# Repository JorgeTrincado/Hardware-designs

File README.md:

# Hardware-designs

This work is licensed under a Creative Commons Attribution-ShareAlike 4.0 International License.

This means you are free to use this design in any way you like (this includes commercial use) as long as you credit me. If you choose to modify the design files, you should share the modified design files under the same license.

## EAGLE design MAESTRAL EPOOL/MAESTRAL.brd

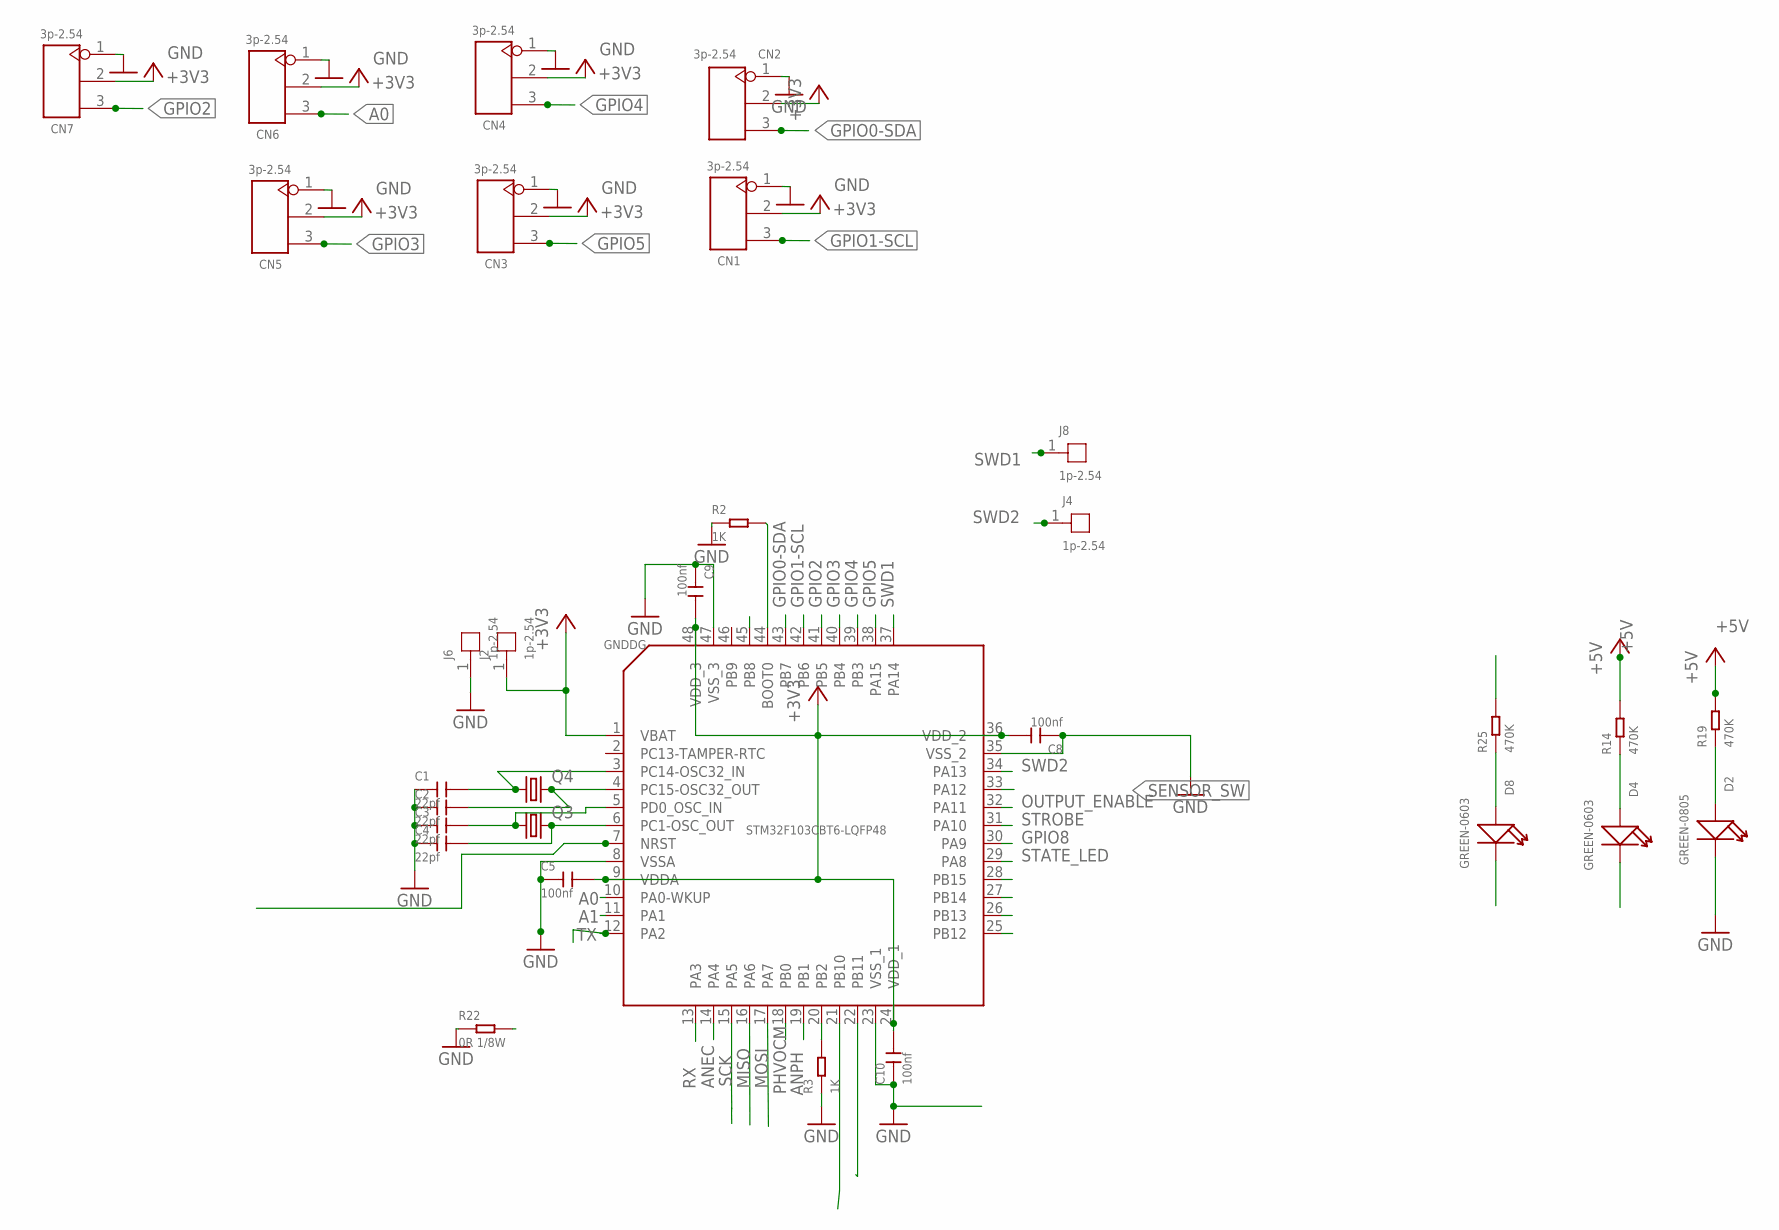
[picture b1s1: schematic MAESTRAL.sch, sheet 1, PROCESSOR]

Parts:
C1, C2, C3, C4: 22pf; C0603
C5, C8, C9, C10: 100nf; C0603
CN1, CN2, CN3, CN4, CN5, CN6, CN7: 3p-2.54; H3-2.54
D2: GREEN-0805; LED-0805
D4, D8: GREEN-0603; LED-0603
GNDDG: STM32F103CBT6-LQFP48; LQFP48-0.5-7X7MM
J2, J4, J6, J8: 1p-2.54; 1P-65/35MIL
Q3: CRYSTALSM49; SM49
Q4: CRYSTALMM20SS; MM20SS
R2, R3: 1K; R0603
R14, R19, R25: 470K; R0603
R22: 0R 1/8W; R0805

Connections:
+3V3: C5.2, C8.2, C9.2, C10.2, CN1.2, CN2.2, CN3.2, CN4.2, CN5.2, CN6.2, CN7.2, GNDDG.1 (VBAT), GNDDG.9 (VDDA), GNDDG.24 (VDD_1), GNDDG.36 (VDD_2), GNDDG.48 (VDD_3), J2.1; also elsewhere on the board
+5V: R14.2, R19.2; also elsewhere on the board
A0: CN6.3, GNDDG.10 (PA0-WKUP)
A1: GNDDG.11 (PA1); also elsewhere on the board
ANEC: GNDDG.14 (PA4); also elsewhere on the board
ANPH: GNDDG.19 (PB1); also elsewhere on the board
ECGND: D4.-; also elsewhere on the board
GND: CN1.1, CN2.1, CN3.1, CN4.1, CN5.1, CN6.1, CN7.1, D2.-, R22.1; also elsewhere on the board
GNDDG: C1.1, C2.1, C3.1, C4.1, C5.1, C8.1, C9.1, C10.1, D8.-, GNDDG.8 (VSSA), GNDDG.23 (VSS_1), GNDDG.35 (VSS_2), GNDDG.47 (VSS_3), J6.1, R2.1, R3.1, R22.2; also elsewhere on the board
GPIO0-SDA: CN2.3, GNDDG.43 (PB7)
GPIO1-SCL: CN1.3, GNDDG.42 (PB6)
GPIO2: CN7.3, GNDDG.41 (PB5)
GPIO3: CN5.3, GNDDG.40 (PB4)
GPIO4: CN4.3, GNDDG.39 (PB3)
GPIO5: CN3.3, GNDDG.38 (PA15)
GPIO8: GNDDG.30 (PA9)
MISO: GNDDG.16 (PA6); also elsewhere on the board
MISO-SDO: GNDDG.27 (PB14); also elsewhere on the board
MOSI: GNDDG.17 (PA7); also elsewhere on the board
MOSI-SDI: GNDDG.28 (PB15); also elsewhere on the board
unnamed: C2.2, GNDDG.4 (PC15-OSC32_OUT), Q4.4 (2)
unnamed: C1.2, GNDDG.3 (PC14-OSC32_IN), Q4.1
unnamed: C4.2, GNDDG.6 (PC1-OSC_OUT), Q3.2
unnamed: C3.2, GNDDG.5 (PD0_OSC_IN), Q3.1
unnamed 35: GNDDG.7 (NRST); also elsewhere on the board
unnamed: GNDDG.20 (PB2), R3.2
unnamed: GNDDG.44 (BOOT0), R2.2
unnamed: D8.+, R25.1
unnamed: GNDDG.45 (PB8), R25.2
unnamed: D4.+, R14.1
unnamed: D2.+, R19.1
OUTPUT_ENABLE: GNDDG.32 (PA11); also elsewhere on the board
PHCS: GNDDG.25 (PB12); also elsewhere on the board
PHVOCM: GNDDG.18 (PB0); also elsewhere on the board
RX: GNDDG.13 (PA3); also elsewhere on the board
SCK: GNDDG.15 (PA5); also elsewhere on the board
SCL2: GNDDG.21 (PB10); also elsewhere on the board
SCLK: GNDDG.26 (PB13); also elsewhere on the board
SDA2: GNDDG.22 (PB11); also elsewhere on the board
SENSOR_SW: GNDDG.33 (PA12); also elsewhere on the board
STATE_LED: GNDDG.29 (PA8)
STROBE: GNDDG.31 (PA10); also elsewhere on the board
SWD1: GNDDG.37 (PA14), J8.1
SWD2: GNDDG.34 (PA13), J4.1
TX: GNDDG.12 (PA2); also elsewhere on the board

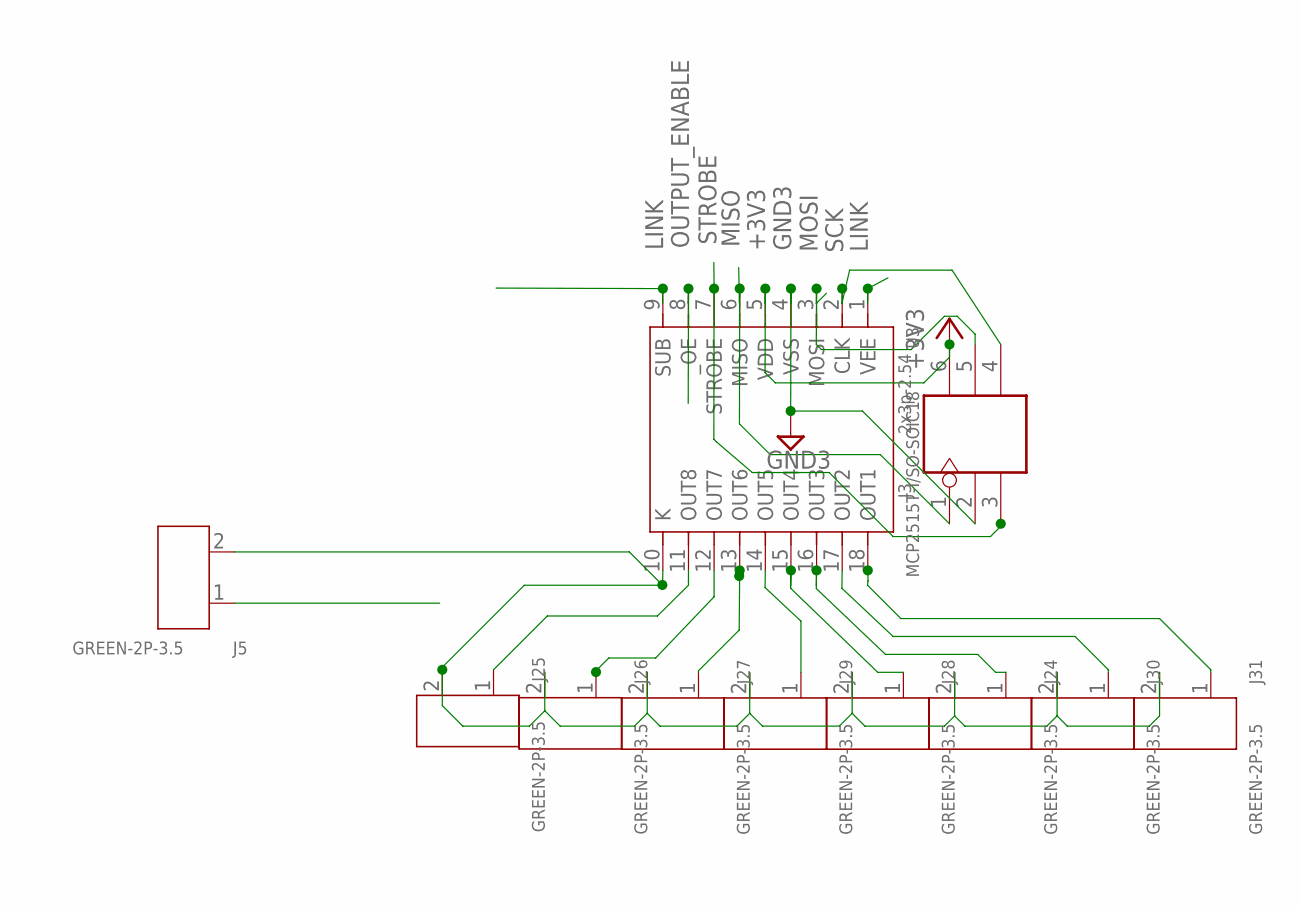
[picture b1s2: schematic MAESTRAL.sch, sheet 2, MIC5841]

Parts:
J3: 2x3p-2.54; H2X3-2.54
J5, J24, J25, J26, J27, J28, J29, J30, J31: GREEN-2P-3.5; H2-3.5-7.0X7.0MM
U3: MCP2515T-I/SO-SOIC18; SOIC18-1.27-11.5X7.5MM

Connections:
+3V3: J3.6, U3.5 (VDD); also elsewhere on the board
GND3: J3.2, U3.4 (VSS)
LINK: J5.1, U3.1 (VEE), U3.9 (SUB)
MISO: J3.1, U3.6 (MISO); also elsewhere on the board
MOSI: J3.5, U3.3 (MOSI); also elsewhere on the board
unnamed: J26.1, U3.12 (OUT7)
unnamed: J27.1, U3.13 (OUT6)
unnamed: J5.2, J24.2, J25.2, J26.2, J27.2, J28.2, J29.2, J30.2, J31.2, U3.10 (K)
unnamed: J29.1, U3.14 (OUT5)
unnamed: J28.1, U3.15 (OUT4)
unnamed: J24.1, U3.16 (OUT3)
unnamed: J30.1, U3.17 (OUT2)
unnamed: J25.1, U3.11 (OUT8)
OUT1: J31.1, U3.18 (OUT1)
OUTPUT_ENABLE: U3.8 (_OE); also elsewhere on the board
SCK: J3.4, U3.2 (CLK); also elsewhere on the board
STROBE: J3.3, U3.7 (STROBE); also elsewhere on the board

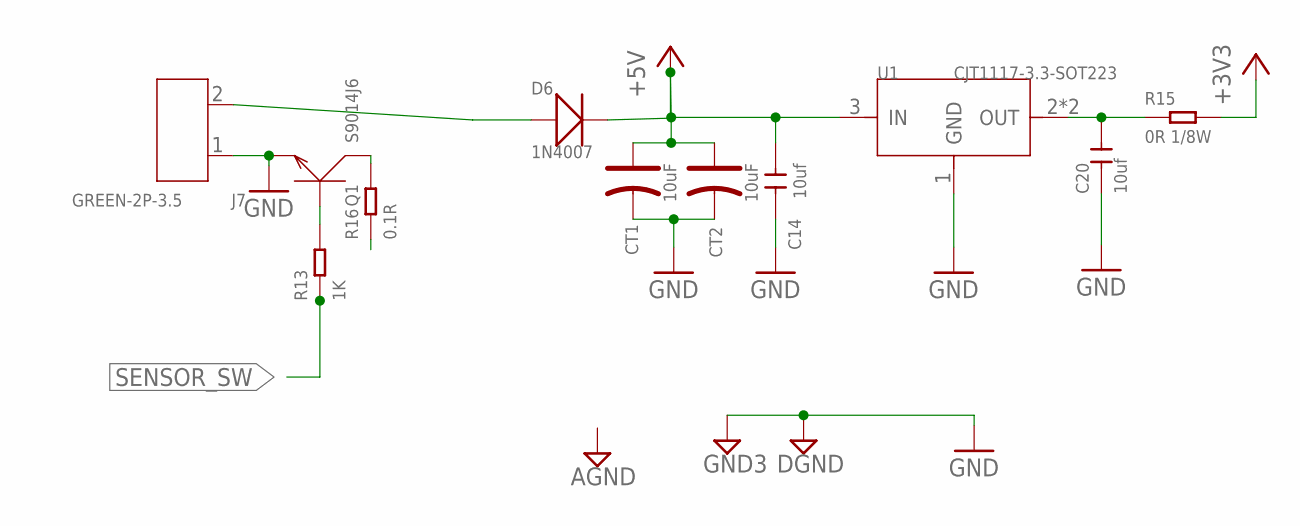
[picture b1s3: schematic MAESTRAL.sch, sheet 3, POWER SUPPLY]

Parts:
C14, C20: 10uf; C0805
CT1, CT2: 10uF; ELECTRO-SMD-C-6MM
D6: 1N4007; DO-214AC
J7: GREEN-2P-3.5; H2-3.5-7.0X7.0MM
Q1: S9014J6; SOT-23
R13: 1K; R0603
R15: 0R 1/8W; R0805
R16: 0.1R; R0805
U1: CJT1117-3.3-SOT223; SOT-223

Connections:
+3V3: R15.2; also elsewhere on the board
+5V: C14.2, CT1.+, CT2.+, D6.2 (-), U1.3 (IN); also elsewhere on the board
ECGND: R16.1; also elsewhere on the board
GND: C14.1, C20.1, CT1.-, CT2.-, J7.1, Q1.2 (E), U1.1 (GND); also elsewhere on the board
INTERRUMPIDO: Q1.3 (C), R16.2
unnamed: D6.1 (+), J7.2
unnamed: C20.2, R15.1, U1.2 (OUT), U1.TER (OUT)
R: Q1.1 (B), R13.2
SENSOR_SW: R13.1; also elsewhere on the board

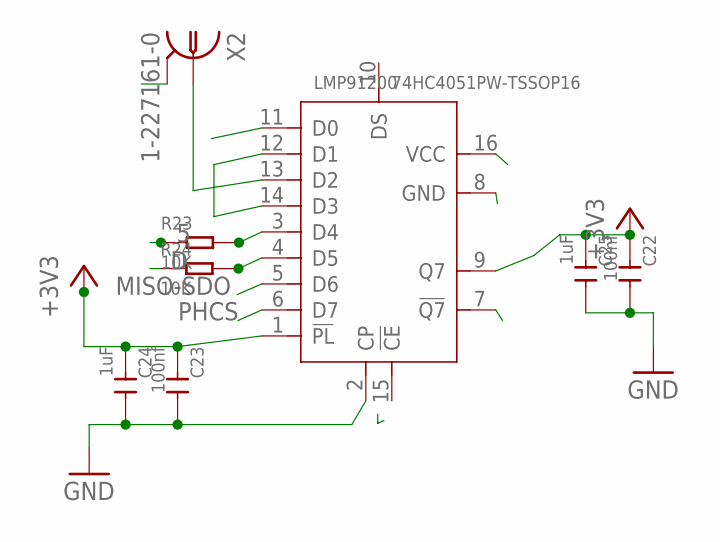
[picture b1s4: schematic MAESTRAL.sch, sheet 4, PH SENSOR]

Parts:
C22, C23: 100nf; C0603
C24, C25: 1uF; C0603
LMP91200: 74HC4051PW-TSSOP16; TSSOP16-0.65-5X4.4MM
R23, R24: 10K; R0603
X2: 1-227161-0; AMP_227161

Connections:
5: LMP91200.3 (D4), R23.2
+3V3: C22.1, C23.1, C24.1, C25.1, LMP91200.1 (!PL), LMP91200.9 (Q7); also elsewhere on the board
ANPH: R24.1; also elsewhere on the board
D: LMP91200.4 (D5), R24.2
GNDDG: C22.2, C23.2, C24.2, C25.2, LMP91200.2 (CP); also elsewhere on the board
MISO-SDO: LMP91200.5 (D6); also elsewhere on the board
MOSI-SDI: LMP91200.8 (GND); also elsewhere on the board
unnamed: LMP91200.12 (D1), LMP91200.14 (D3)
unnamed: LMP91200.13 (D2), X2.1
PHCS: LMP91200.6 (D7); also elsewhere on the board
PHVOCM: R23.1; also elsewhere on the board
SCLK: LMP91200.7 (!Q7); also elsewhere on the board
VCM: LMP91200.16 (VCC), X2.2

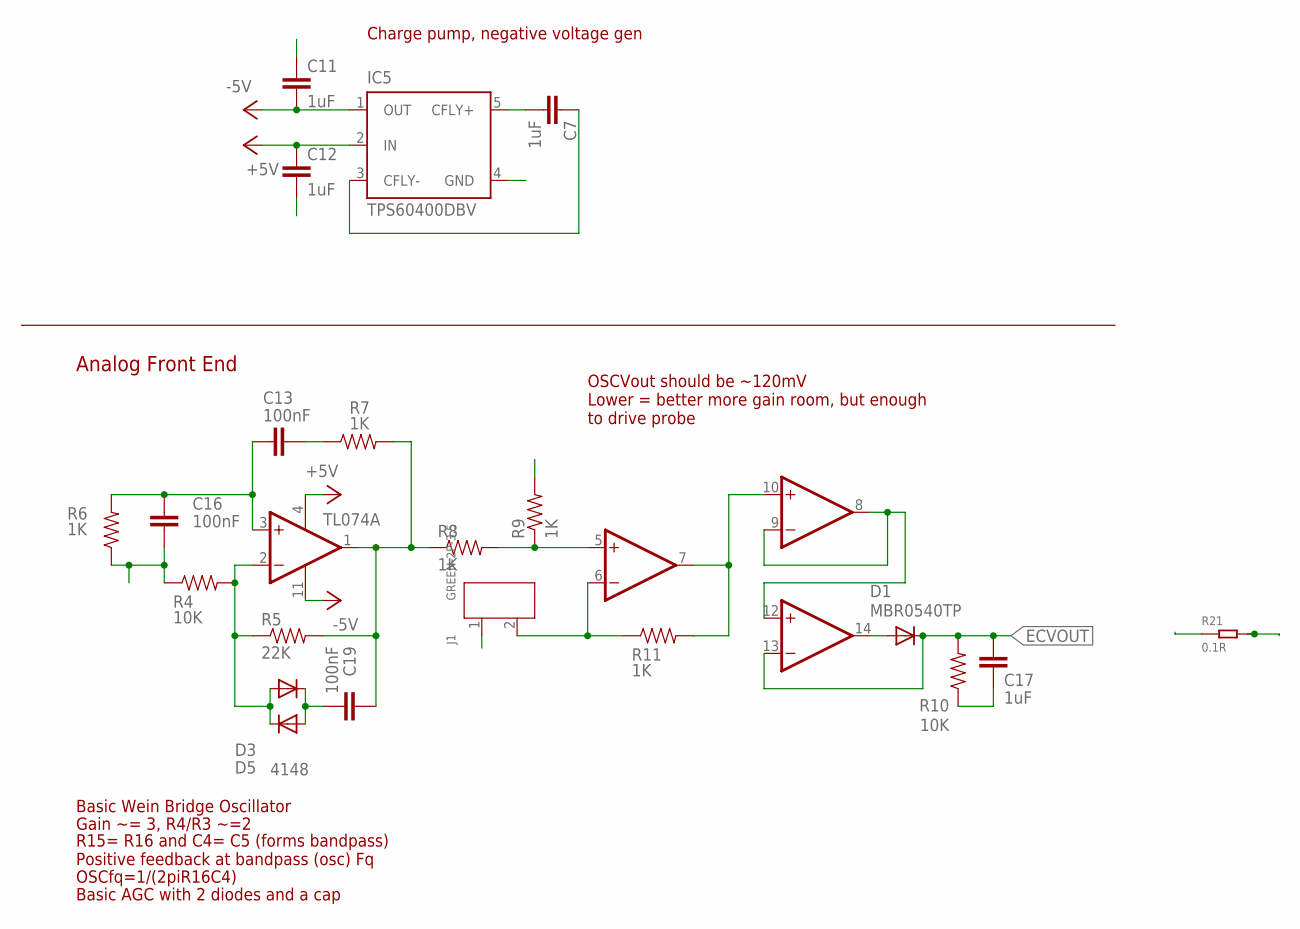
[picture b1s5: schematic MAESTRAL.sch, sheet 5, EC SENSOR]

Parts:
C7, C11, C12, C17: 1uF; 0805
C13, C16, C19: 100nF; 0805
D1: MBR0540TP; SOD123
D3, D5: 4148; SOD123
IC5: TPS60400DBV; SOT23-DBV
J1: GREEN-2P-3.5; H2-3.5-7.0X7.0MM
R4, R10: 10K; 0805
R5: 22K; 0805
R6, R7, R8, R9, R11: 1K; 0805
R21: 0.1R; R0805
TL074: TL074; SO14

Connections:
+5V: C12.1, IC5.2 (IN), TL074.4 (V+); also elsewhere on the board
-5V: C11.2, IC5.1 (OUT), TL074.11 (V-)
ANEC: R21.2; also elsewhere on the board
ECGND: C11.1, C12.2, C16.1, C17.1, IC5.4 (GND), J1.1, R4.1, R6.1, R9.2, R10.1; also elsewhere on the board
ECVOUT: C17.2, D1.C, R10.2, R21.1, TL074.13 (-IN)
unnamed: R11.2, TL074.7 (OUT), TL074.10 (+IN)
unnamed: D1.A, TL074.14 (OUT)
unnamed: C19.2, D3.C, D5.A
unnamed: C7.1, IC5.3 (CFLY-)
unnamed: C7.2, IC5.5 (CFLY+)
unnamed: C13.2, C16.2, R6.2, TL074.3 (+IN)
unnamed: D3.A, D5.C, R4.2, R5.1, TL074.2 (-IN)
unnamed: C13.1, R7.1
unnamed: C19.1, R5.2, R7.2, R8.1, TL074.1 (OUT)
unnamed: R8.2, R9.1, TL074.5 (+IN)
unnamed: J1.2, R11.1, TL074.6 (-IN)
unnamed: TL074.8 (OUT), TL074.9 (-IN), TL074.12 (+IN)

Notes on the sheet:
Charge pump, negative voltage gen
Analog Front End
Basic Wein Bridge Oscillator
Gain ~= 3, R4/R3 ~=2
R15= R16 and C4= C5 (forms bandpass) Positive feedback at bandpass (osc) Fq
OSCfq=1/(2piR16C4)
Basic AGC with 2 diodes and a cap
OSCVout should be ~120mV Lower = better more gain room, but enough to drive probe

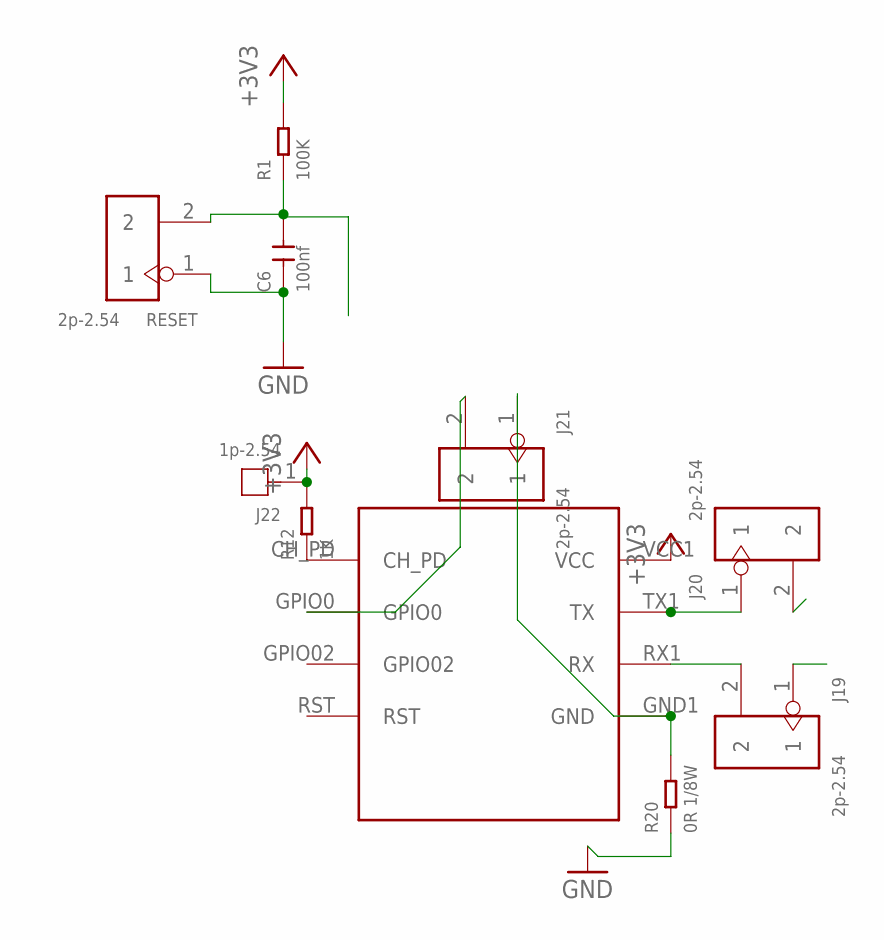
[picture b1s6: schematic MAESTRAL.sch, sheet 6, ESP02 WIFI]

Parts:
C6: 100nf; C0603
J19, J20, J21: 2p-2.54; H2-2.54
J22: 1p-2.54; 1P-65/35MIL
R1: 100K; R0603
R12: 1K; R0603
R20: 0R 1/8W; R0805
RESET: 2p-2.54; H2-2.54
U$1: ESP-03; ESP

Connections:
+3V3: J22.1, R1.2, R12.2, U$1.VCC1 (VCC); also elsewhere on the board
GND: R20.1; also elsewhere on the board
GNDDG: C6.1, RESET.1; also elsewhere on the board
unnamed 35: C6.2, R1.1, RESET.2; also elsewhere on the board
unnamed: R12.1, U$1.CH_PD
unnamed: J21.1, R20.2, U$1.GND1 (GND)
unnamed: J20.1, U$1.TX1 (TX)
unnamed: J19.2, U$1.RX1 (RX)
unnamed: J21.2, U$1.GPIO0
RX: J19.1; also elsewhere on the board
TX: J20.2; also elsewhere on the board

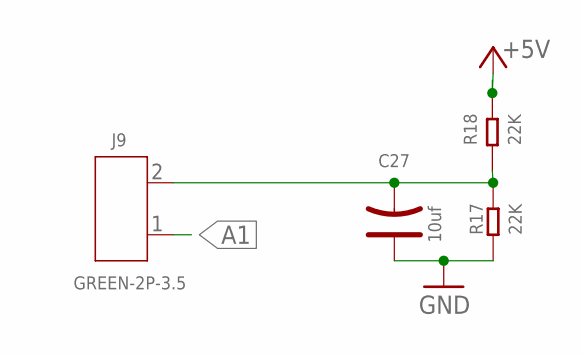
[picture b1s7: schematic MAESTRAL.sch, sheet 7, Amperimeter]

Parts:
C27: 10uf; AVX-A
J9: GREEN-2P-3.5; H2-3.5-7.0X7.0MM
R17, R18: 22K; R0603

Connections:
+5V: R18.2; also elsewhere on the board
A1: J9.1; also elsewhere on the board
GND: C27.+, R17.1; also elsewhere on the board
unnamed: C27.-, J9.2, R17.2, R18.1

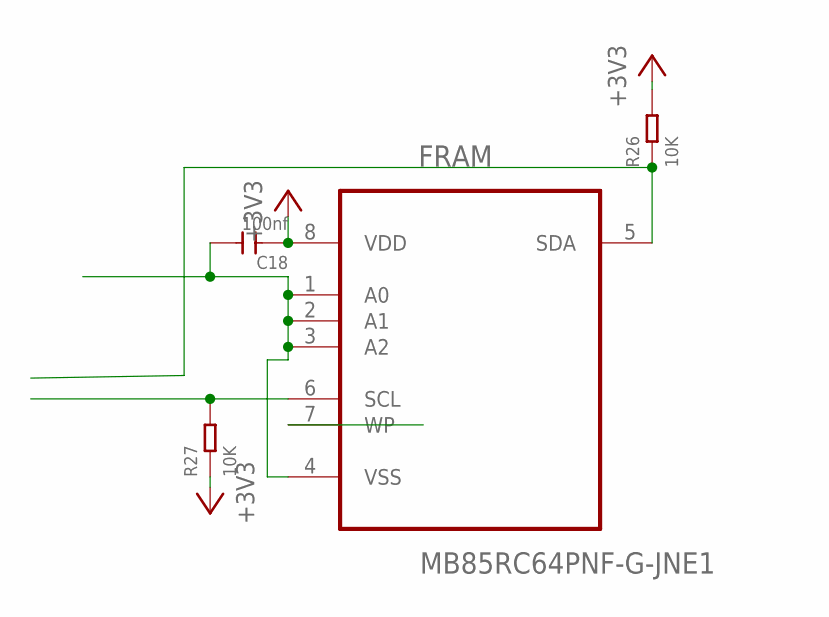
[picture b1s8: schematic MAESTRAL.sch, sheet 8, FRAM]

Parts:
C18: 100nf; C0603
FRAM: MB85RC64PNF-G-JNE1; SOIC127P600X175-8N
R26, R27: 10K; R0603

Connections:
+3V3: C18.1, FRAM.7 (WP), FRAM.8 (VDD), R26.2, R27.1; also elsewhere on the board
GNDDG: C18.2, FRAM.1 (A0), FRAM.2 (A1), FRAM.3 (A2), FRAM.4 (VSS); also elsewhere on the board
SCL2: FRAM.6 (SCL), R27.2; also elsewhere on the board
SDA2: FRAM.5 (SDA), R26.1; also elsewhere on the board

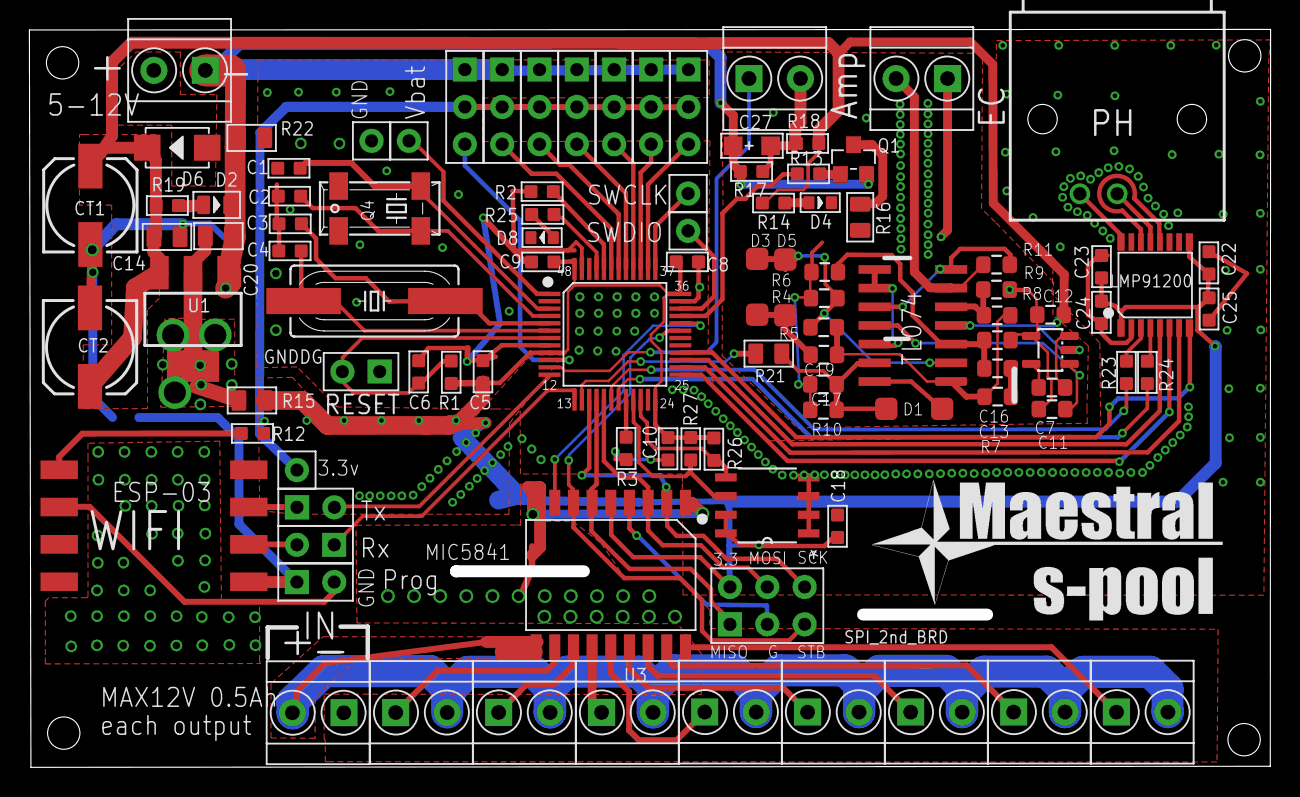
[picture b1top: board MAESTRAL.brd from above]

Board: 2 copper layers, 83.6 x 49.4 mm, 101 parts (1 on the bottom side), 83 nets.

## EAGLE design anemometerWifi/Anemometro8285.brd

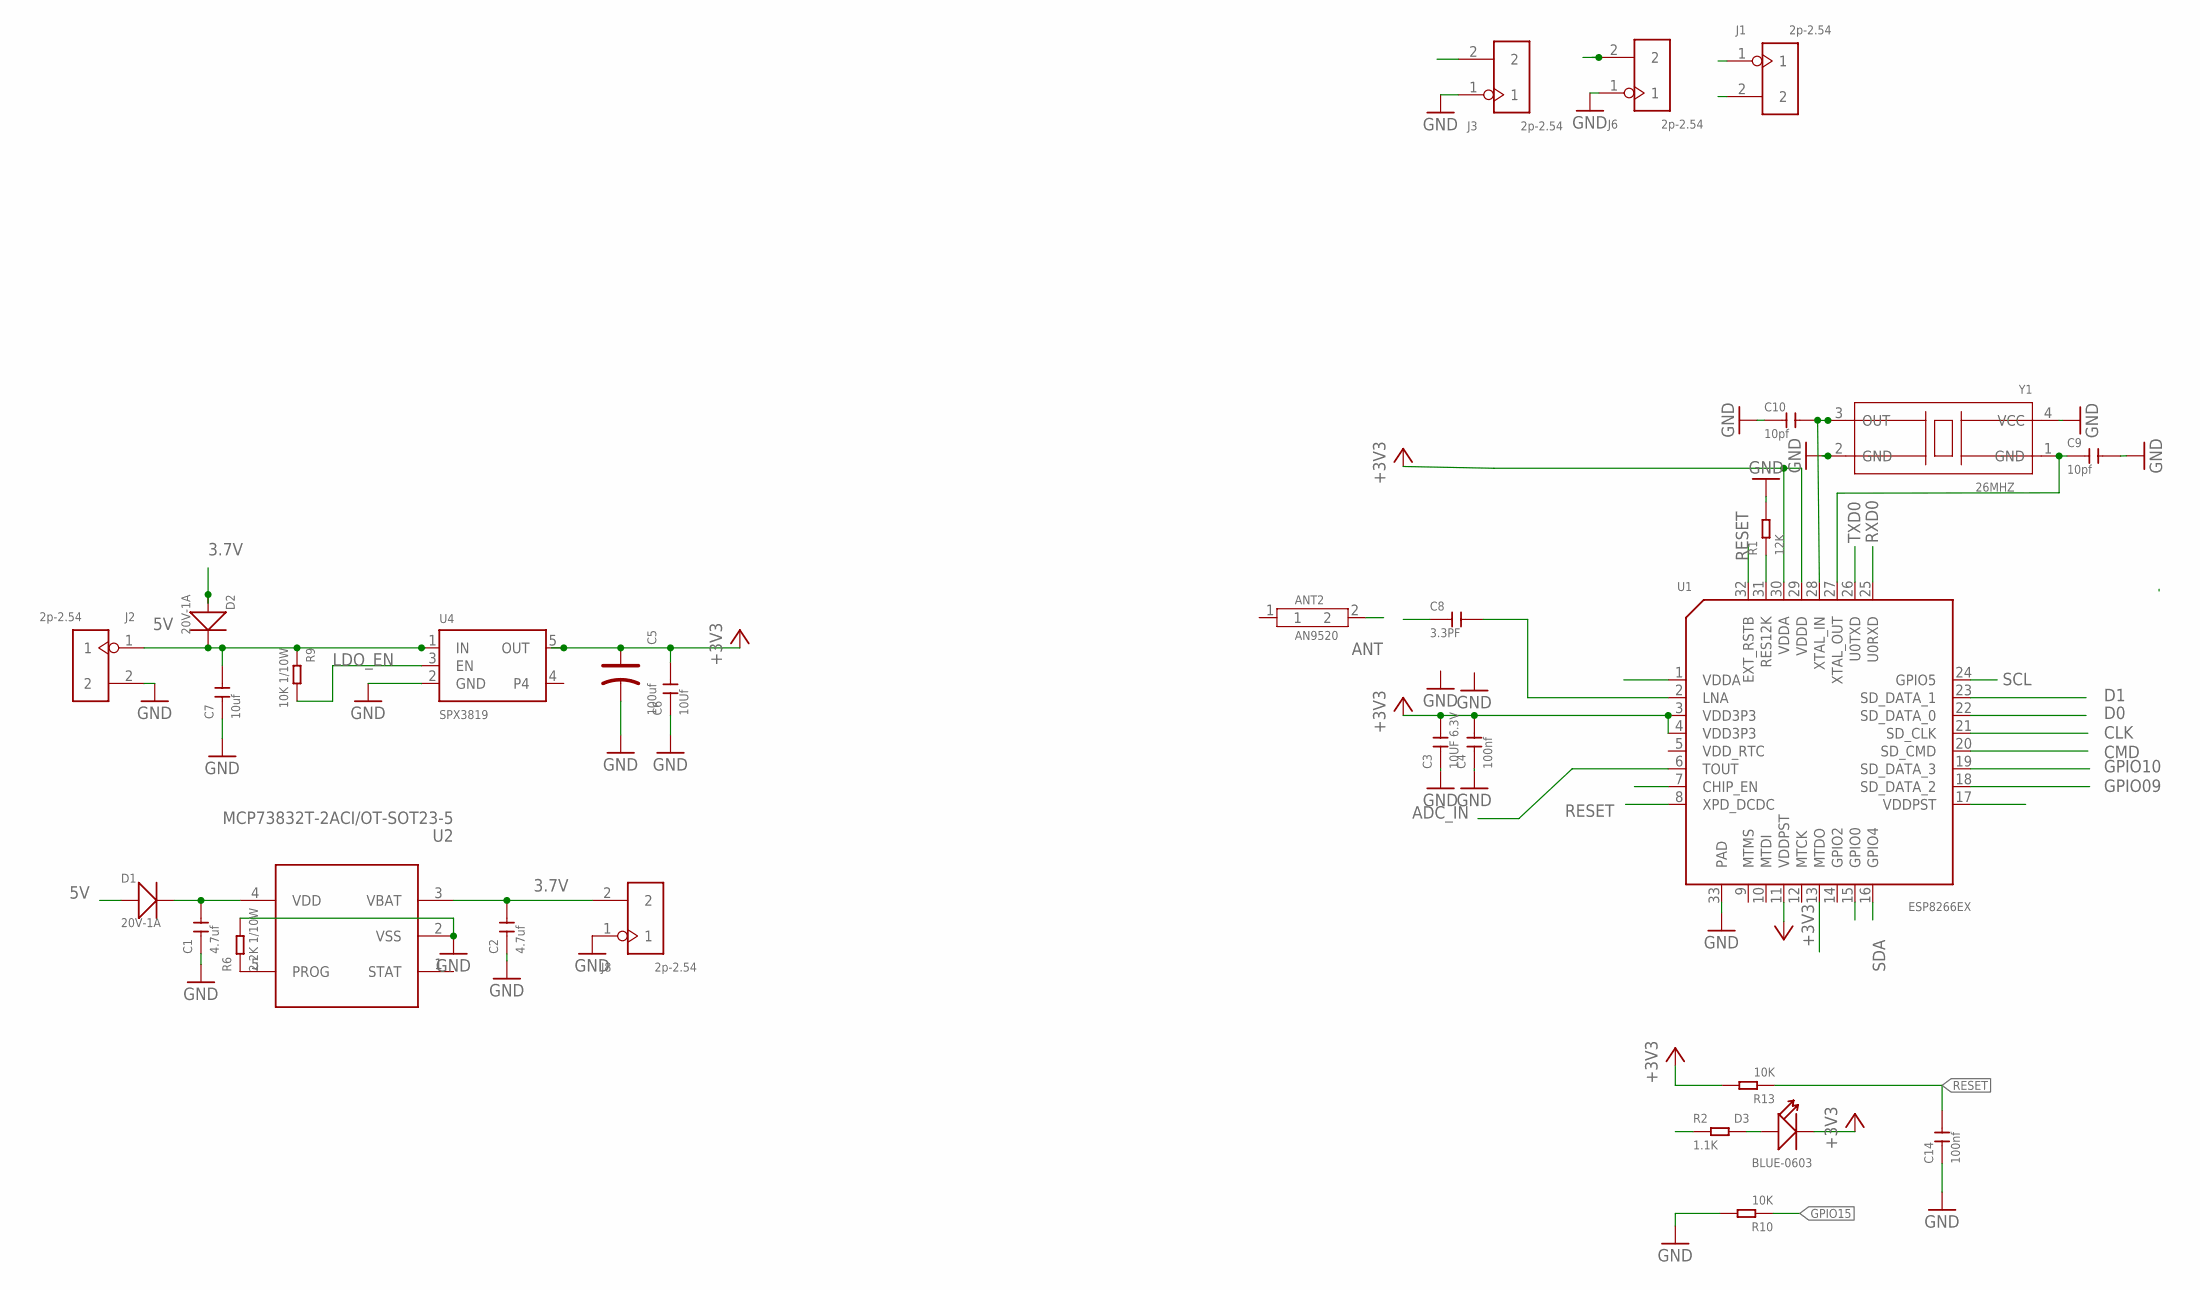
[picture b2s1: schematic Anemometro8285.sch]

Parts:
ANT2: AN9520; ANT2-SMD-9.5X2X1.2MM
C1, C2: 4.7uf; C0603
C3: 10UF 6.3V; C0603
C4, C14: 100nf; C0603
C5: 100uf; AVX-B
C6: 10Uf; C0603
C7: 10uf; C0805
C8: 3.3PF; C0603
C9, C10: 10pf; C0603
D1, D2: 20V-1A; SOD-123
D3: BLUE-0603; LED-0603
J1, J2, J3, J6, J8: 2p-2.54; H2-2.54
R1: 12K; R0603
R2: 1.1K; R0603
R6: 2.2K 1/10W; R0603
R9: 10K 1/10W; R0603
R10, R13: 10K; R0603
U1: ESP8266EX; QFN32G-0.5-5X5MM
U2: MCP73832T-2ACI/OT-SOT23-5; SOT-23-5
U4: SPX3819; SOT23-5
Y1: 26MHZ; X4-SMD-2.5X2.0X0.5MM

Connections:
3.7V: C2.2, D2.+, J8.2, U2.3 (VBAT)
5V: C7.2, D1.+, D2.-, J2.1, R9.1, U4.1 (IN)
+3V3: C3.2, C4.2, C5.+, C6.2, D3.-, R13.2, U1.1 (VDDA), U1.3 (VDD3P3), U1.4 (VDD3P3), U1.7 (CHIP_EN), U1.11 (VDDPST), U1.17 (VDDPST), U1.29 (VDDD), U1.30 (VDDA), U4.5 (OUT)
ADC_IN: U1.6 (TOUT)
ANT: ANT2.2, C8.1
CLK: U1.21 (SD_CLK)
CMD: U1.20 (SD_CMD)
D0: U1.22 (SD_DATA_0)
D1: U1.23 (SD_DATA_1)
GND: C1.1, C2.1, C3.1, C4.1, C5.-, C6.1, C7.1, C9.2, C10.1, C14.1, J2.2, J3.1, J6.1, J8.1, R1.2, R6.2, R10.2, U1.33 (PAD), U2.2 (VSS), U4.2 (GND), Y1.2 (GND), Y1.4 (VCC)
GPIO0: J3.2, U1.15 (GPIO0)
GPIO09: U1.18 (SD_DATA_2)
GPIO10: U1.19 (SD_DATA_3)
GPIO15: R10.1, U1.13 (MTDO)
LDO_EN: R9.2, U4.3 (EN)
unnamed: C8.2, U1.2 (LNA)
unnamed: R6.1, U2.5 (PROG)
unnamed: C9.1, U1.27 (XTAL_OUT), Y1.1 (GND)
unnamed: R1.1, U1.31 (RES12K)
unnamed: C10.2, U1.28 (XTAL_IN), Y1.3 (OUT)
unnamed: D3.+, R2.2
unnamed: C1.2, D1.-, U2.4 (VDD)
RESET: C14.2, R13.1, U1.8 (XPD_DCDC), U1.32 (EXT_RSTB)
RXD0: J1.2, U1.25 (U0RXD)
SCL: J6.2, U1.24 (GPIO5)
SDA: U1.16 (GPIO4)
TXD0: J1.1, R2.1, U1.26 (U0TXD)

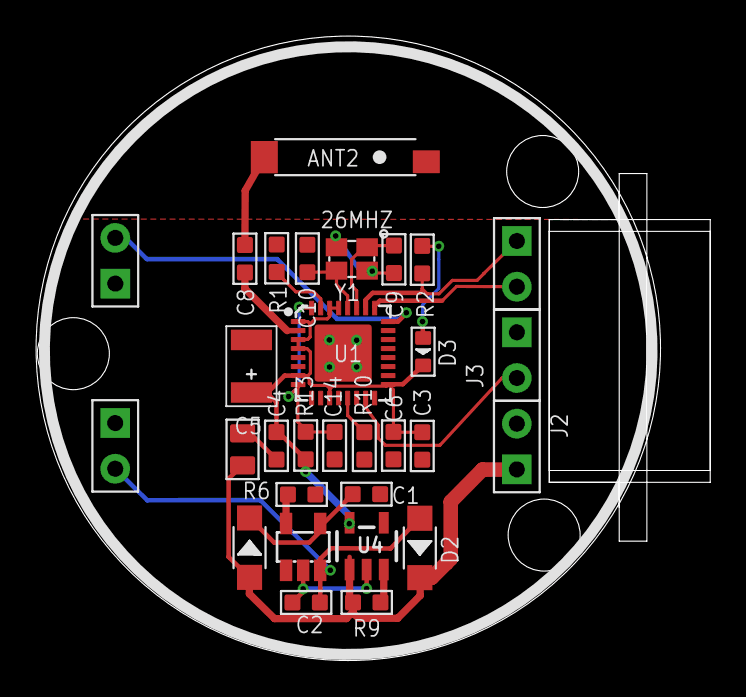
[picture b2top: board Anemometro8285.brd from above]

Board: 2 copper layers, 37.4 x 34.7 mm, 30 parts (0 on the bottom side), 19 nets.

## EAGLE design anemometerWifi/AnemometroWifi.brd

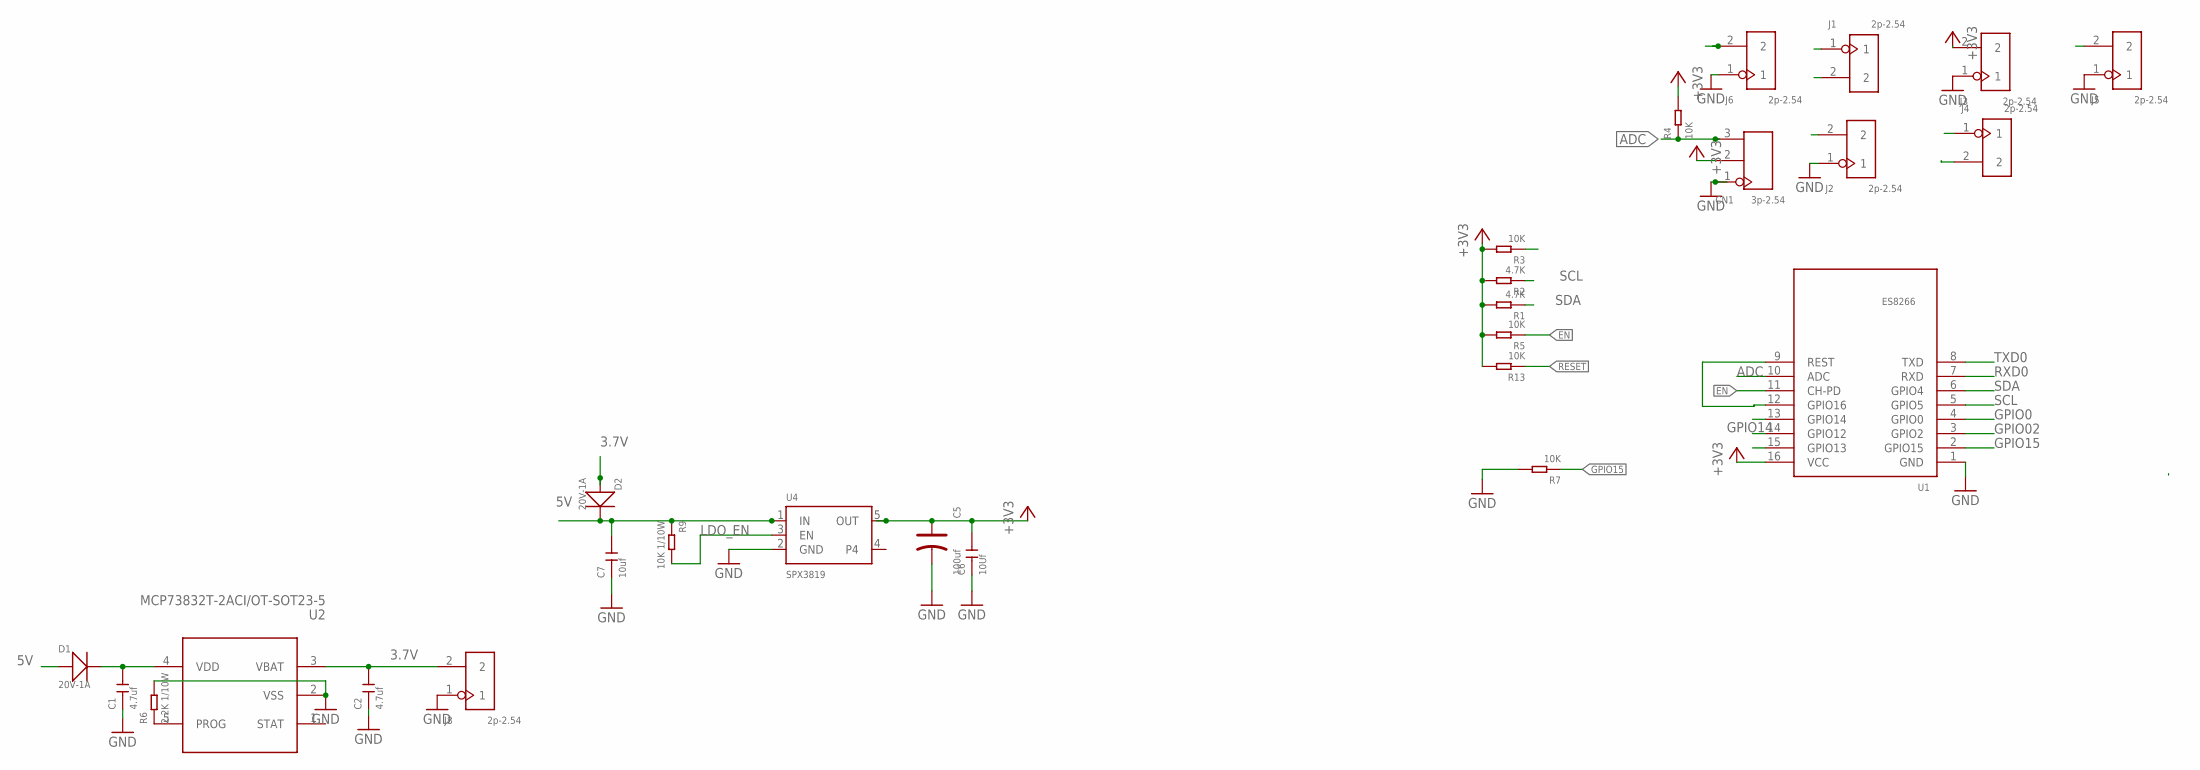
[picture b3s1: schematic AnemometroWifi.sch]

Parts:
C1, C2: 4.7uf; C0603
C5: 100uf; AVX-B
C6: 10Uf; C0603
C7: 10uf; C0805
CN1: 3p-2.54; H3-2.54
D1, D2: 20V-1A; SOD-123
J1, J2, J3, J4, J5, J6, J8: 2p-2.54; H2-2.54
R1, R2: 4.7K; R0603
R3, R4, R5, R7, R13: 10K; R0603
R6: 2.2K 1/10W; R0603
R9: 10K 1/10W; R0603
U1: ES8266; LGA16-2.0-24X16MM
U2: MCP73832T-2ACI/OT-SOT23-5; SOT-23-5
U4: SPX3819; SOT23-5

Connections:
3.7V: C2.2, D2.+, J8.2, U2.3 (VBAT)
5V: C7.2, D1.+, D2.-, J5.2, R9.1, U4.1 (IN)
+3V3: C5.+, C6.2, CN1.2, J3.2, R1.2, R2.2, R3.2, R4.2, R5.2, R13.2, U1.16 (VCC), U4.5 (OUT)
ADC: CN1.3, R4.1, U1.10 (ADC)
EN: R5.1, U1.11 (CH-PD)
GND: C1.1, C2.1, C5.-, C6.1, C7.1, CN1.1, J2.1, J3.1, J5.1, J6.1, J8.1, R6.2, R7.2, U1.1 (GND), U2.2 (VSS), U4.2 (GND)
GPIO0: J6.2, U1.4 (GPIO0)
GPIO02: U1.3 (GPIO2)
GPIO12: U1.14 (GPIO12)
GPIO13: U1.15 (GPIO13)
GPIO14: J2.2, R3.1, U1.13 (GPIO14)
GPIO15: R7.1, U1.2 (GPIO15)
LDO_EN: R9.2, U4.3 (EN)
unnamed: R6.1, U2.5 (PROG)
unnamed: C1.2, D1.-, U2.4 (VDD)
RESET: R13.1, U1.9 (REST), U1.12 (GPIO16)
RXD0: J1.2, U1.7 (RXD)
SCL: J4.1, R2.1, U1.5 (GPIO5)
SDA: J4.2, R1.1, U1.6 (GPIO4)
TXD0: J1.1, U1.8 (TXD)

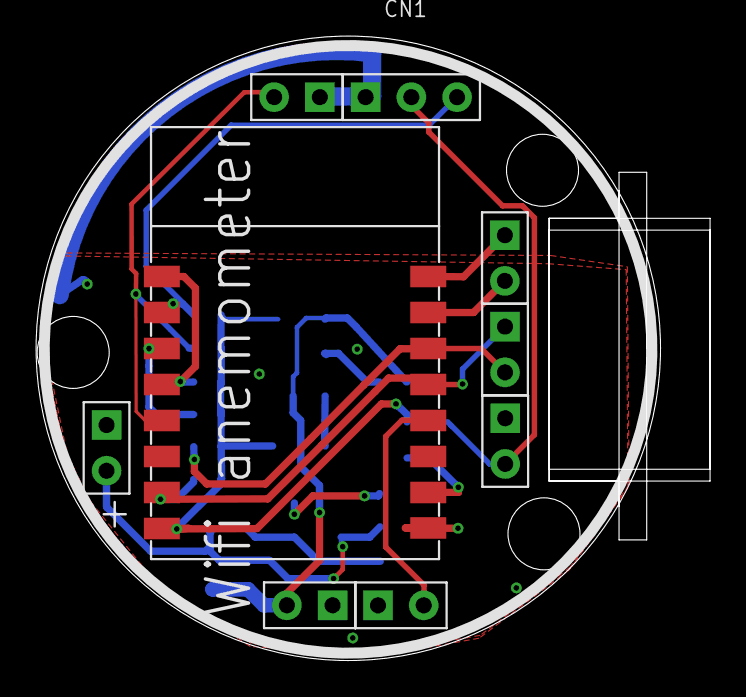
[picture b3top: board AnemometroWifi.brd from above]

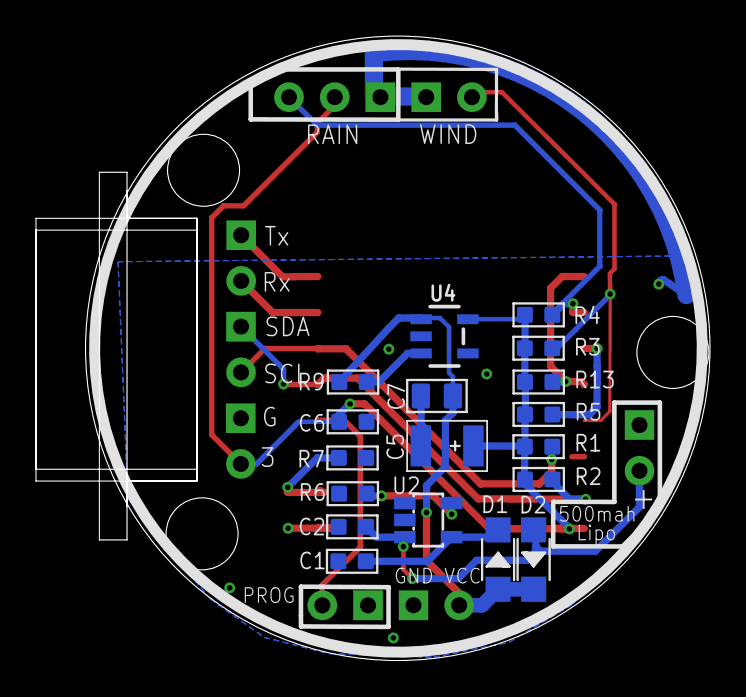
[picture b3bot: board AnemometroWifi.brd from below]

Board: 2 copper layers, 37.4 x 34.7 mm, 27 parts (18 on the bottom side), 17 nets.

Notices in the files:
parts and their libraries:
microbuilder: This work is placed in the public domain, and may be freely used for commercial and non-commercial work with the following conditions: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
